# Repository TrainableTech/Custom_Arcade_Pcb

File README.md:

# Custom_Arcade_Pcb
Arduino based custom pcb design for arcade machine

The custom PCB layout is Arduino nano based/ Changes can be made for using Nano esp in future project 

The basic design integrates the following subsystems into a unified board:
The board includes a Timer pinout, a Sensor pin, StartB pin, 2 Relay outputs, an LEDs pinout, a ticket pinout, extra pinouts, and power pins.
Software used: Kicad 9.0

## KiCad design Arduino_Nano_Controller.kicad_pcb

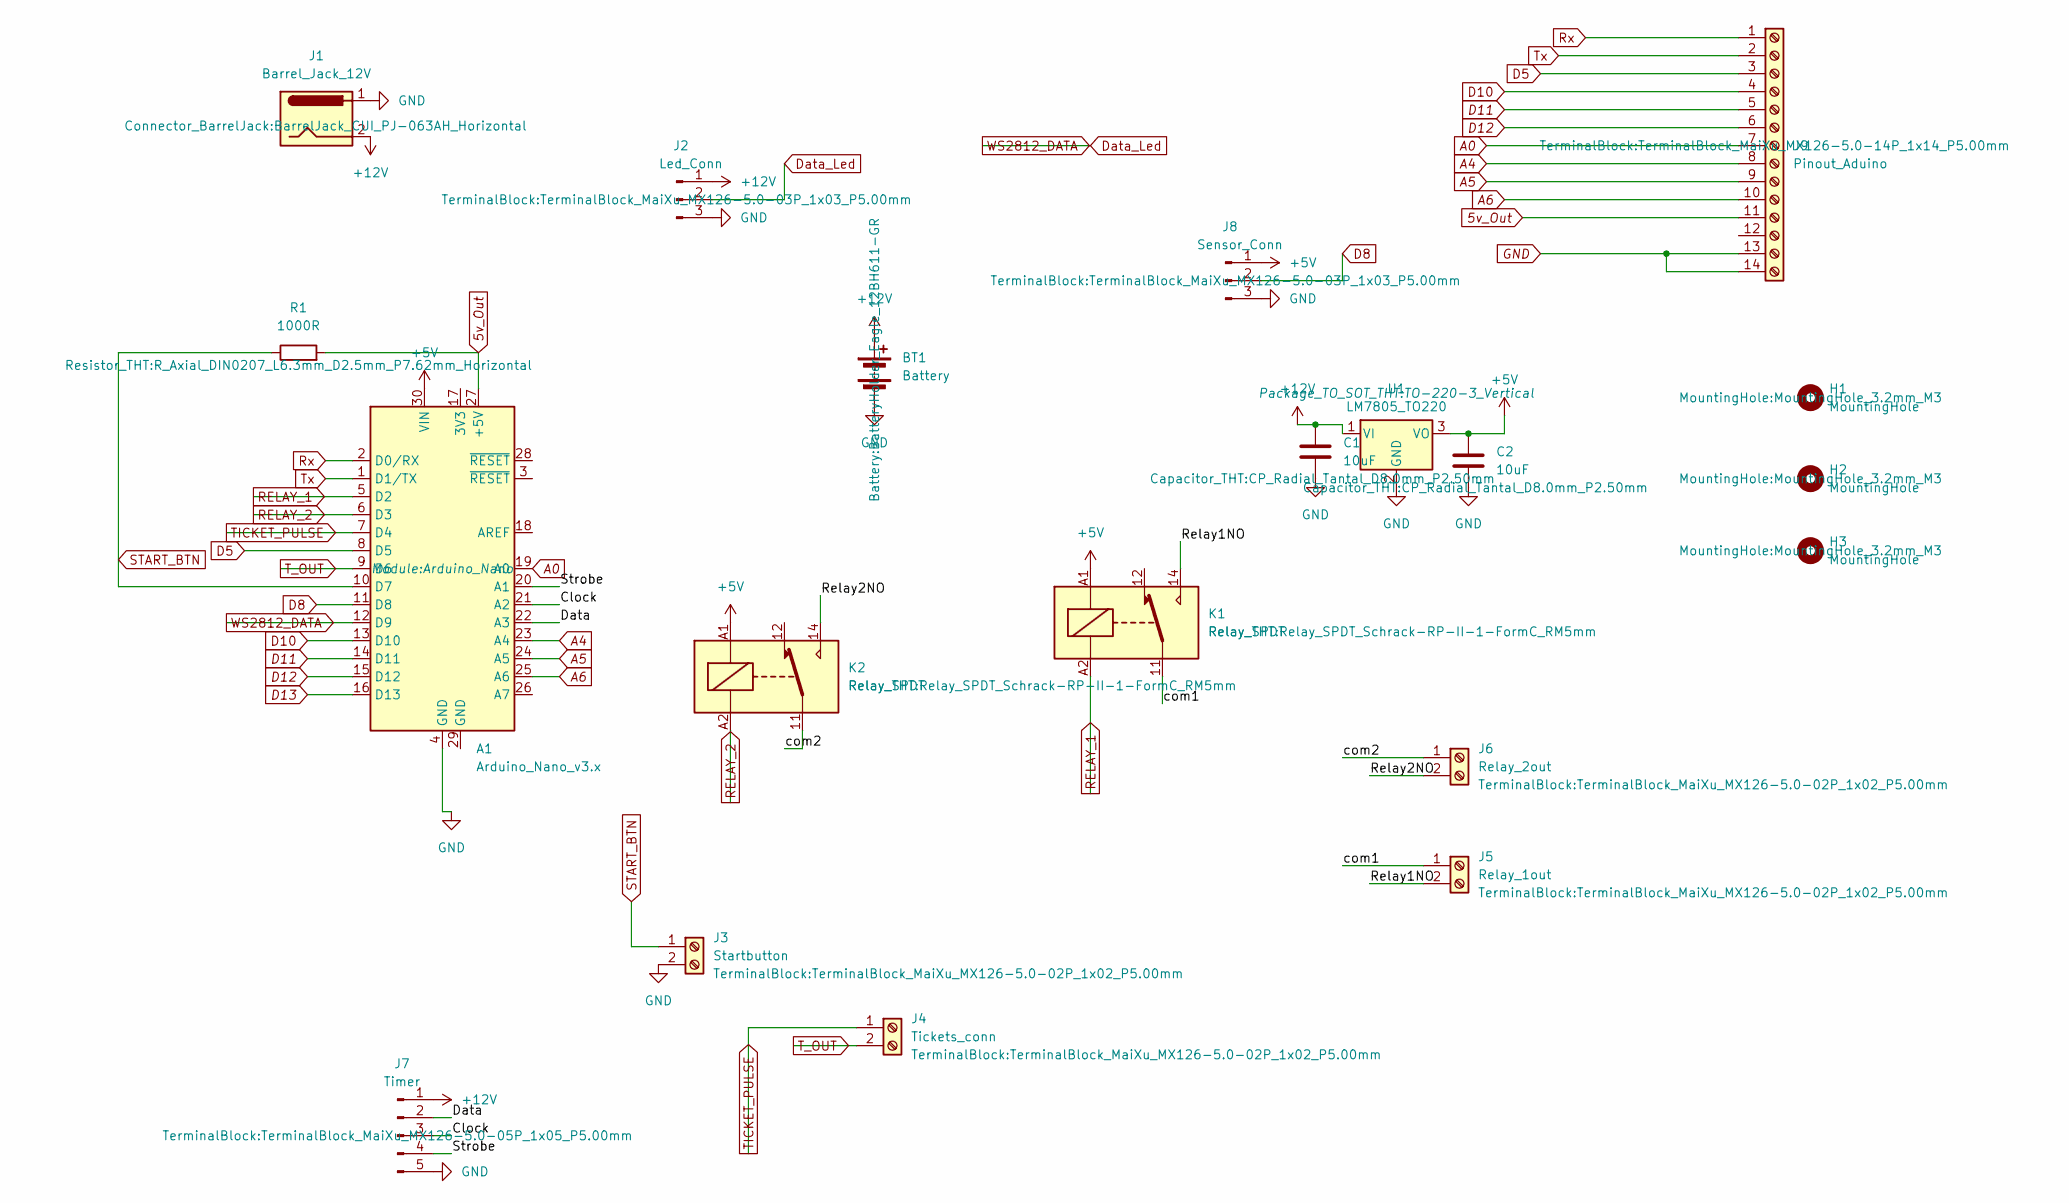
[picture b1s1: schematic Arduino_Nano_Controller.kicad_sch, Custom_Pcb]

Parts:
A1: Arduino_Nano_v3.x; Arduino_Nano
BT1: Battery; BatteryHolder_Eagle_12BH611-GR
C1, C2: 10uF; CP_Radial_Tantal_D8.0mm_P2.50mm
H1, H2, H3: MountingHole; MountingHole_3.2mm_M3
J1: Barrel_Jack_12V; BarrelJack_CUI_PJ-063AH_Horizontal
J2: Led_Conn; TerminalBlock_MaiXu_MX126-5.0-03P_1x03_P5.00mm
J3: Startbutton; TerminalBlock_MaiXu_MX126-5.0-02P_1x02_P5.00mm
J4: Tickets_conn; TerminalBlock_MaiXu_MX126-5.0-02P_1x02_P5.00mm
J5: Relay_1out; TerminalBlock_MaiXu_MX126-5.0-02P_1x02_P5.00mm
J6: Relay_2out; TerminalBlock_MaiXu_MX126-5.0-02P_1x02_P5.00mm
J7: Timer; TerminalBlock_MaiXu_MX126-5.0-05P_1x05_P5.00mm
J8: Sensor_Conn; TerminalBlock_MaiXu_MX126-5.0-03P_1x03_P5.00mm
J9: Pinout_Aduino; TerminalBlock_MaiXu_MX126-5.0-14P_1x14_P5.00mm
K1, K2: Relay_SPDT; Relay_SPDT_Schrack-RP-II-1-FormC_RM5mm
R1: 1000R; R_Axial_DIN0207_L6.3mm_D2.5mm_P7.62mm_Horizontal
U1: LM7805_TO220; TO-220-3_Vertical

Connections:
5v_Out: A1.27 (+5V), J9.11, R1.2
+5V: A1.30 (VIN), C2.1, J8.1, K1.A1, K2.A1, U1.3 (VO)
+12V: BT1.1 (+), C1.1, J1.2, J2.1, J7.1, U1.1 (VI)
/Clock: A1.21 (A2), J7.3
/Data: A1.22 (A3), J7.2
/Relay1NO: J5.2, K1.14
/Relay2NO: J6.2, K2.14
/Strobe: A1.20 (A1), J7.4
/com1: J5.1, K1.11
/com2: J6.1, K2.11
A0: A1.19 (A0), J9.7
A4: A1.23 (A4), J9.8
A5: A1.24 (A5), J9.9
A6: A1.25 (A6), J9.10
D5: A1.8 (D5), J9.3
D8: A1.11 (D8), J8.2
D10: A1.13 (D10), J9.4
D11: A1.14 (D11), J9.5
D12: A1.15 (D12), J9.6
D13: A1.16 (D13)
Data_Led: A1.12 (D9), J2.2
GND: A1.4 (GND), BT1.2 (-), C1.2, C2.2, J1.1, J2.3, J3.2, J7.5, J8.3, J9.13, J9.14, U1.2 (GND)
RELAY_1: A1.5 (D2), K1.A2
RELAY_2: A1.6 (D3), K2.A2
Rx: A1.2 (D0/RX), J9.1
START_BTN: A1.10 (D7), J3.1, R1.1
TICKET_PULSE: A1.7 (D4), J4.1
T_OUT: A1.9 (D6), J4.2
Tx: A1.1 (D1/TX), J9.2

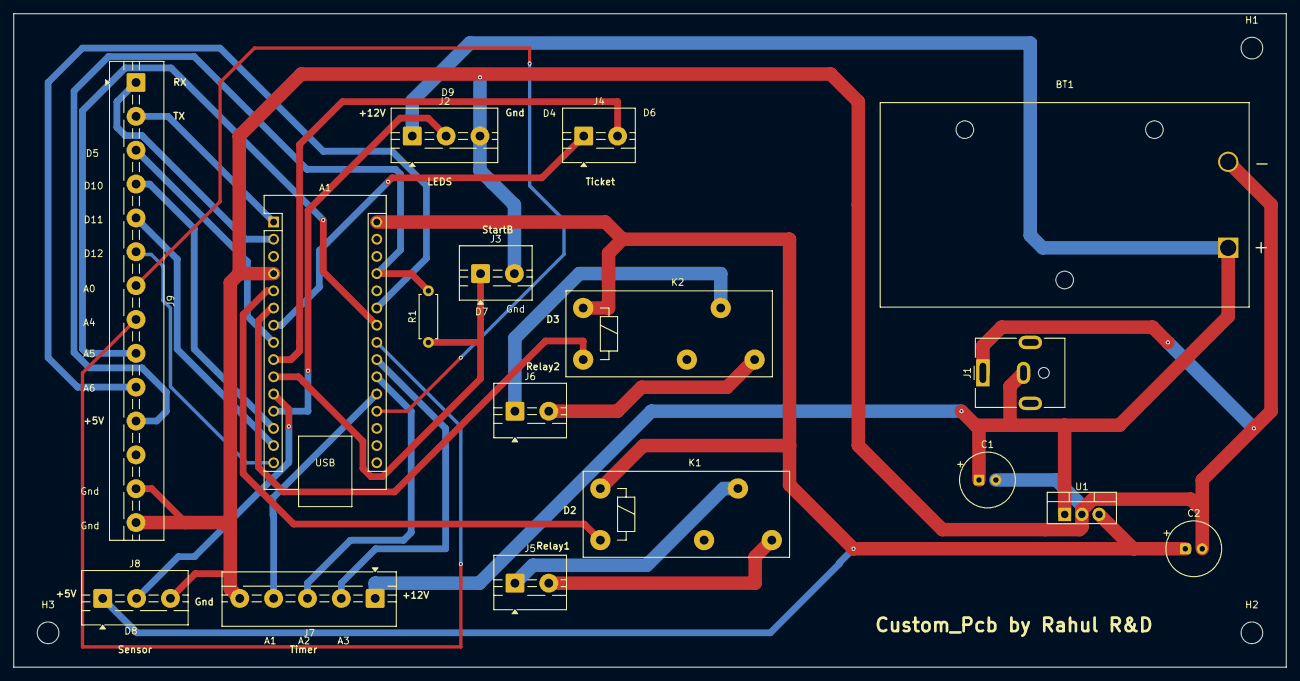
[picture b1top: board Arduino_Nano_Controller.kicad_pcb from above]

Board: 2 copper layers, 188.0 x 96.5 mm, 20 parts (0 on the bottom side), 28 nets.

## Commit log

2026-06-23 Add files via upload
    Kicad custom pcb
